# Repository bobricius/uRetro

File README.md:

# μRetro
https://hackaday.io/project/164736-retro-game-console-with-cpu-on-fake-sd-cards

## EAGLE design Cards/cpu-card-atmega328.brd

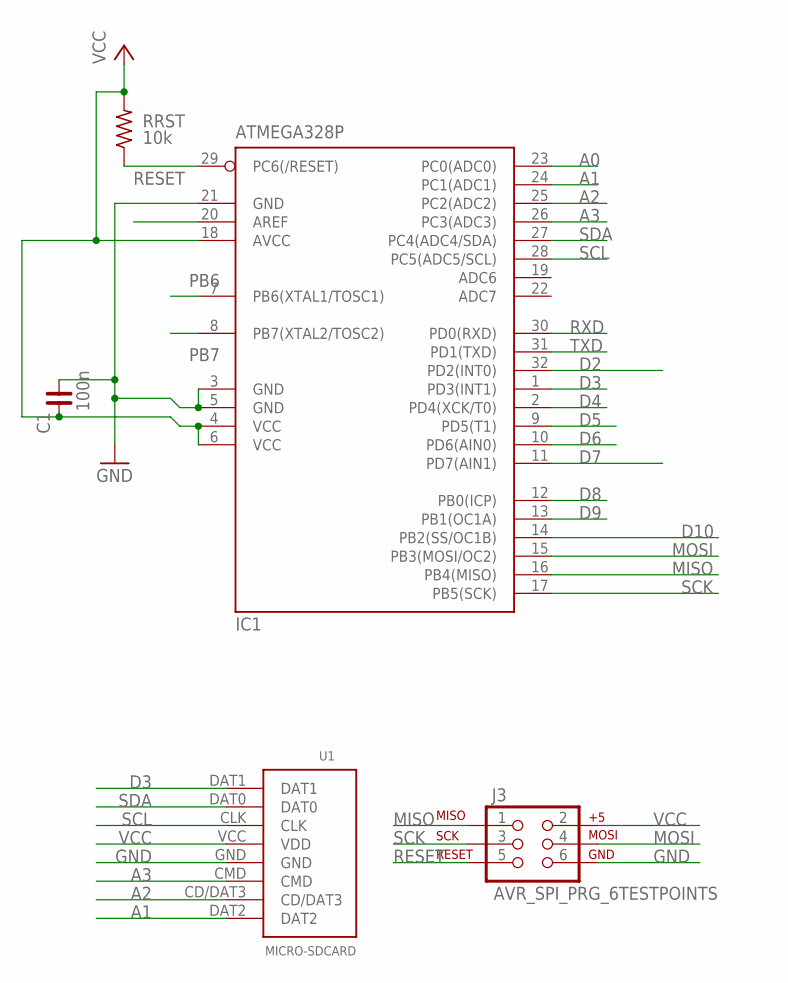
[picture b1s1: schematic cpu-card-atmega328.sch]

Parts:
C1: 100n; C0603
IC1: ATMEGA328P; TQFP32-08
J3: AVR_SPI_PRG_6TESTPOINTS; 2X3_TEST_POINTS
RRST: 10k; R0603@1
U1: MICRO-SDCARD

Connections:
A0: IC1.23 (PC0(ADC0))
A1: IC1.24 (PC1(ADC1)), U1.DAT2
A2: IC1.25 (PC2(ADC2)), U1.CD/DAT3
A3: IC1.26 (PC3(ADC3)), U1.CMD
AREF: IC1.20 (AREF)
D2: IC1.32 (PD2(INT0))
D3: IC1.1 (PD3(INT1)), U1.DAT1
D4: IC1.2 (PD4(XCK/T0))
D5: IC1.9 (PD5(T1))
D6: IC1.10 (PD6(AIN0))
D7: IC1.11 (PD7(AIN1))
D8: IC1.12 (PB0(ICP))
D9: IC1.13 (PB1(OC1A))
D10: IC1.14 (PB2(SS/OC1B))
GND: C1.1, IC1.3 (GND), IC1.5 (GND), IC1.21 (GND), J3.6, U1.GND
MISO: IC1.16 (PB4(MISO)), J3.1
MOSI: IC1.15 (PB3(MOSI/OC2)), J3.4
PB6: IC1.7 (PB6(XTAL1/TOSC1))
PB7: IC1.8 (PB7(XTAL2/TOSC2))
RESET: IC1.29 (PC6(/RESET)), J3.5, RRST.1
RXD: IC1.30 (PD0(RXD))
SCK: IC1.17 (PB5(SCK)), J3.3
SCL: IC1.28 (PC5(ADC5/SCL)), U1.CLK
SDA: IC1.27 (PC4(ADC4/SDA)), U1.DAT0
TXD: IC1.31 (PD1(TXD))
VCC: C1.2, IC1.4 (VCC), IC1.6 (VCC), IC1.18 (AVCC), J3.2, RRST.2, U1.VCC (VDD)

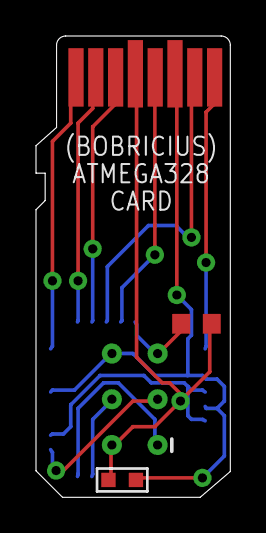
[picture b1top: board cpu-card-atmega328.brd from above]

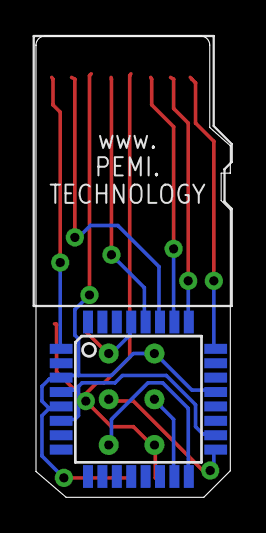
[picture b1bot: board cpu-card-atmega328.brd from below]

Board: 2 copper layers, 10.8 x 25.6 mm, 5 parts (2 on the bottom side), 12 nets.

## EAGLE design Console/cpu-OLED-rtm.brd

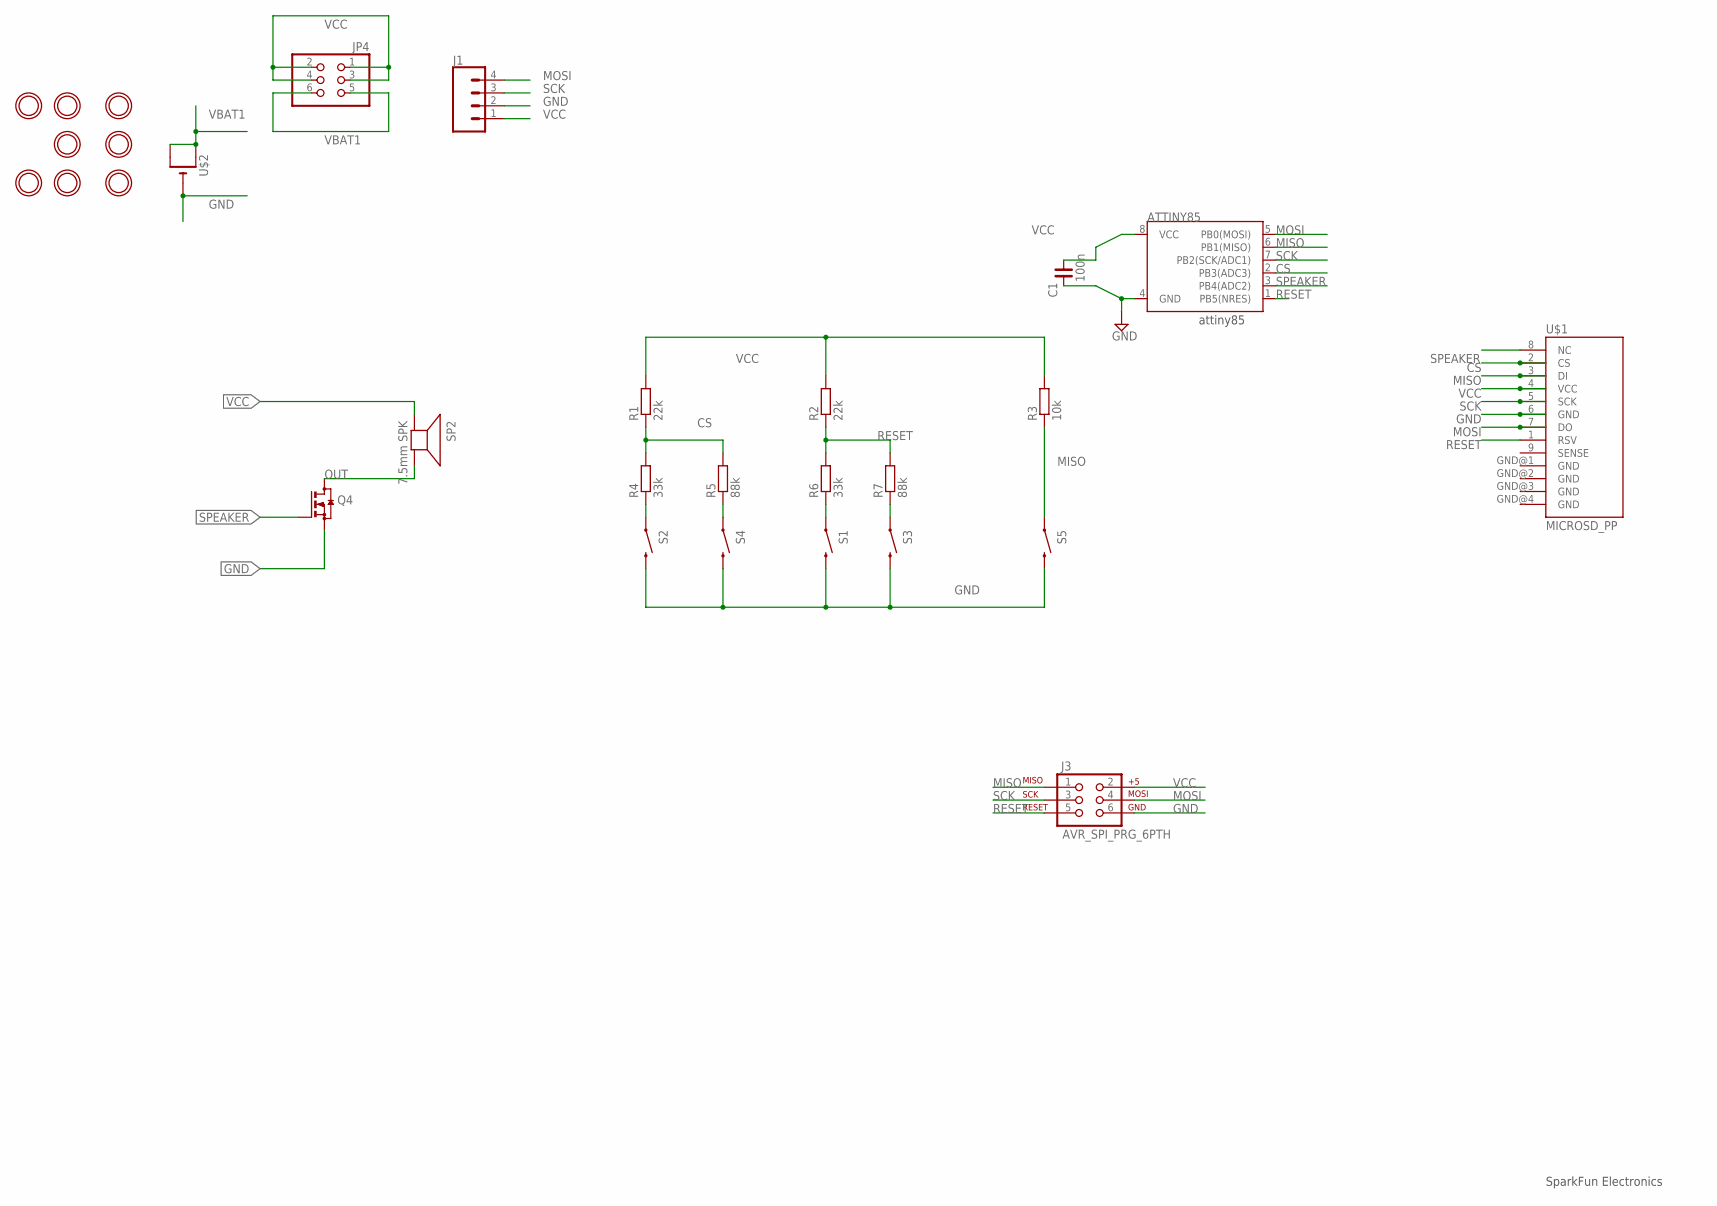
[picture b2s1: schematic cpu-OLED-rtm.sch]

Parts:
ATTINY85: ATTINY45; SO08-EIAJ
C1: 100n; C0805
J1: CONN_041X04_NO_SILK; 1X04_NO_SILK
J3: AVR_SPI_PRG_6PTH; 2X3
JP4: PINHD-2X3; 2X03
Q4: BSS123; SOT23
R1, R2: 22k; R0805
R3: 10k; R0805
R4, R6: 33k; R0805
R5, R7: 88k; R0805
S1, S2, S3, S4, S5: SWITCH-MOMENTARY-2SMD-4; TACTILE_SWITCH_TALL
SP2: 7.5mm SPK; BUZZER_SMT_5MM
U$1: MICROSD_PP
U$2: CR2032THM; CR2032-THRU
U$3, U$4, U$5, U$6, U$7, U$8, U$9, U$11: MOUNTINGHOLE2.0; MOUNTINGHOLE_2.0_PLATED

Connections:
CS: ATTINY85.2 (PB3(ADC3)), R1.1, R4.2, R5.2, U$1.2 (CS)
GND: ATTINY85.4 (GND), C1.2, J1.2, J3.6, Q4.2 (S), S1.B2 (2), S2.B2 (2), S3.B2 (2), S4.B2 (2), S5.B2 (2), U$1.6 (GND), U$2.-
MISO: ATTINY85.6 (PB1(MISO)), J3.1, R3.1, S5.A2 (1), U$1.3 (DI)
MOSI: ATTINY85.5 (PB0(MOSI)), J1.4, J3.4, U$1.7 (DO)
unnamed: R4.1, S2.A2 (1)
unnamed: R5.1, S4.A2 (1)
unnamed: R6.1, S1.A2 (1)
unnamed: R7.1, S3.A2 (1)
OUT: Q4.3 (D), SP2.-
RESET: ATTINY85.1 (PB5(NRES)), J3.5, R2.1, R6.2, R7.2, U$1.1 (RSV)
SCK: ATTINY85.7 (PB2(SCK/ADC1)), J1.3, J3.3, U$1.5 (SCK)
SPEAKER: ATTINY85.3 (PB4(ADC2)), Q4.1 (G), U$1.8 (NC)
VBAT1: JP4.5, JP4.6, U$2.+1 (+), U$2.+2 (+1)
VCC: ATTINY85.8 (VCC), C1.1, J1.1, J3.2, JP4.1, JP4.2, JP4.3, JP4.4, R1.2, R2.2, R3.2, SP2.+, U$1.4 (VCC)

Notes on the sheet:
SparkFun Electronics
attiny85

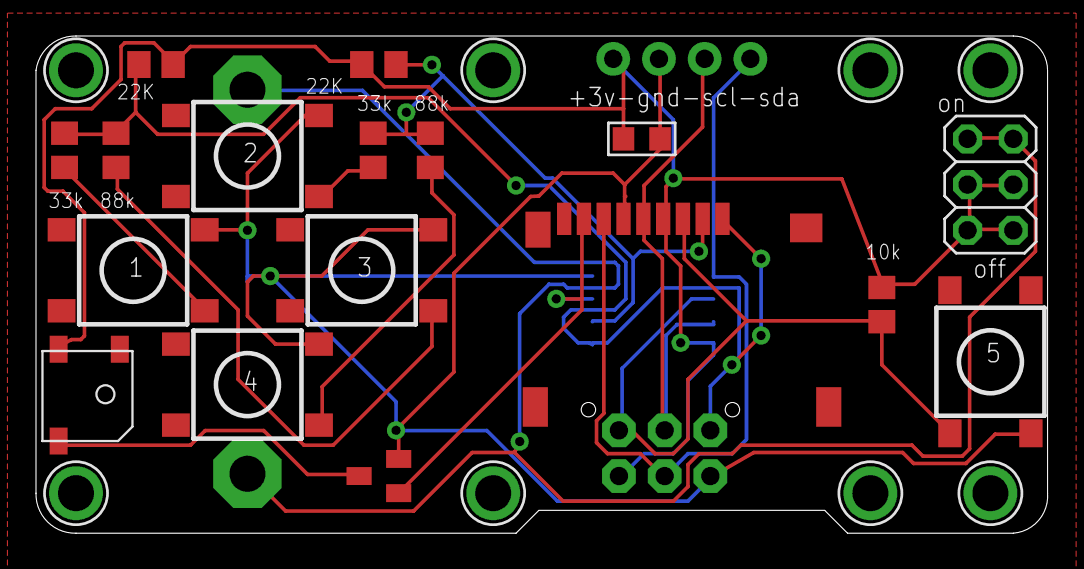
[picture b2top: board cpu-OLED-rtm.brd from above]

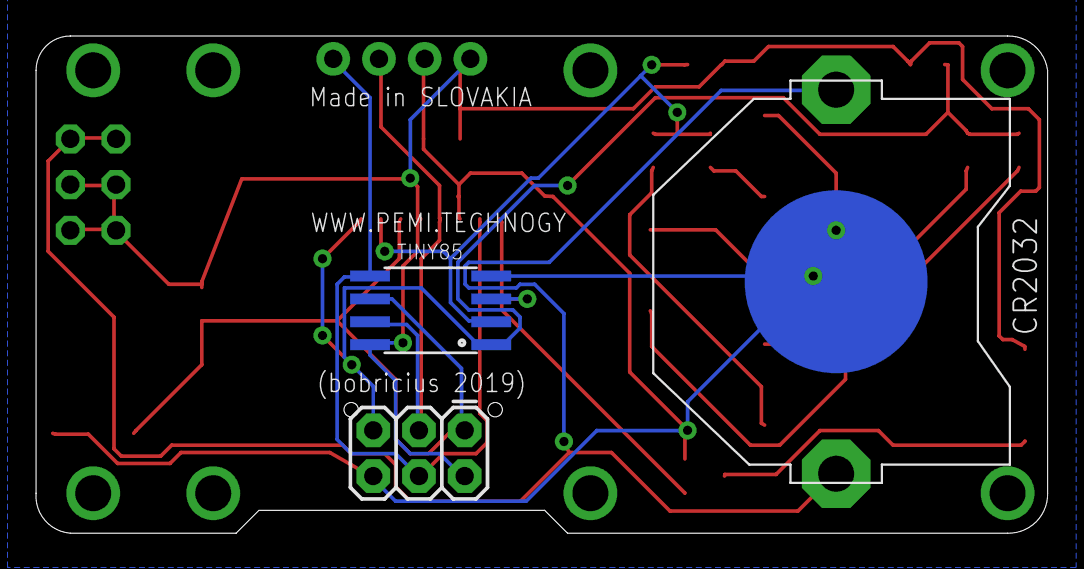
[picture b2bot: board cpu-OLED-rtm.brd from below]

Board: 2 copper layers, 56.2 x 27.6 mm, 29 parts (3 on the bottom side), 14 nets.

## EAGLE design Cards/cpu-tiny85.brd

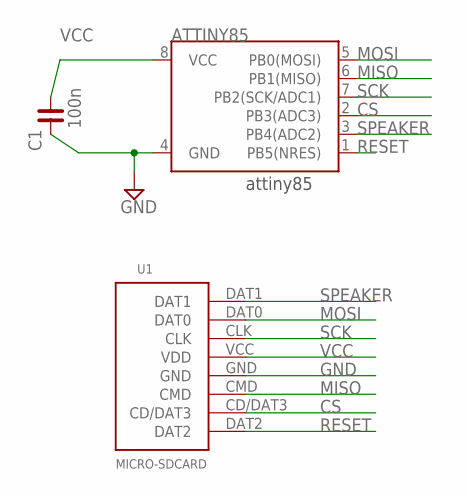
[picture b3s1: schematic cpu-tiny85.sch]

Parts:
ATTINY85: ATTINY45; SO08-EIAJ
C1: 100n; C0603
U1: MICRO-SDCARD

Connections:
CS: ATTINY85.2 (PB3(ADC3)), U1.CD/DAT3
GND: ATTINY85.4 (GND), C1.2, U1.GND
MISO: ATTINY85.6 (PB1(MISO)), U1.CMD
MOSI: ATTINY85.5 (PB0(MOSI)), U1.DAT0
RESET: ATTINY85.1 (PB5(NRES)), U1.DAT2
SCK: ATTINY85.7 (PB2(SCK/ADC1)), U1.CLK
SPEAKER: ATTINY85.3 (PB4(ADC2)), U1.DAT1
VCC: ATTINY85.8 (VCC), C1.1, U1.VCC (VDD)

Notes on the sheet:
attiny85

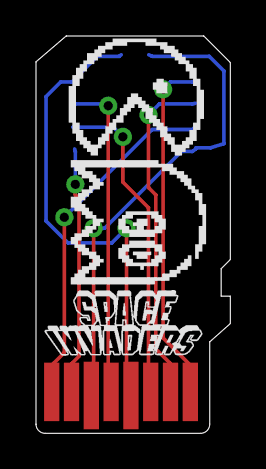
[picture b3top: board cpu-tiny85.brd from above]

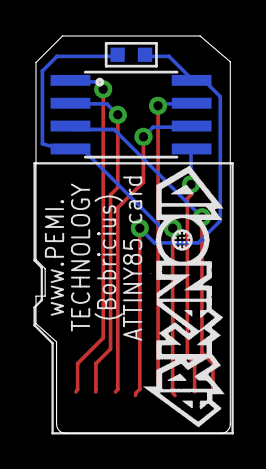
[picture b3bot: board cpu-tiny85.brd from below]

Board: 2 copper layers, 10.8 x 22.1 mm, 3 parts (3 on the bottom side), 8 nets.

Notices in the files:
parts and their libraries:
SparkFun-Connectors: Licensing: Creative Commons ShareAlike 4.0 International - https://creativecommons.org/licenses/by-sa/4.0
SparkFun-Electromechanical: Licensing: CC v3.0 Share-Alike You are welcome to use this library for commercial purposes.
